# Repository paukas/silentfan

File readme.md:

This is a relay based fan controller.

Arduino switches a relay via pin `PIN_CTL`. Relay inputs are connected to 5V (relay on) and 12V (relay off). Switching is based on temperature received from PC over Serail PORT. PC writes GPU temperature as string to serial port on regular intervals. If arduino fails to receive or parse temperature reading it goes to an error state and switches relay back to 12V.

Possible error state scenarios:
* Arduino failed to receive temperature readings `MAX_NOSIGNALCNT=5` or more times
* Arduino failed to parse temperature reading
* Temperature reading was out of range [`TEMP_MINPOSSIBLE=25`, `TEMP_MAXPOSSIBLE=80`]

Arduino switches relay on only when temperature is below `TEMP_LOW=50`. It switches relay off if temperature reches `TEMP_HIGH=55`.

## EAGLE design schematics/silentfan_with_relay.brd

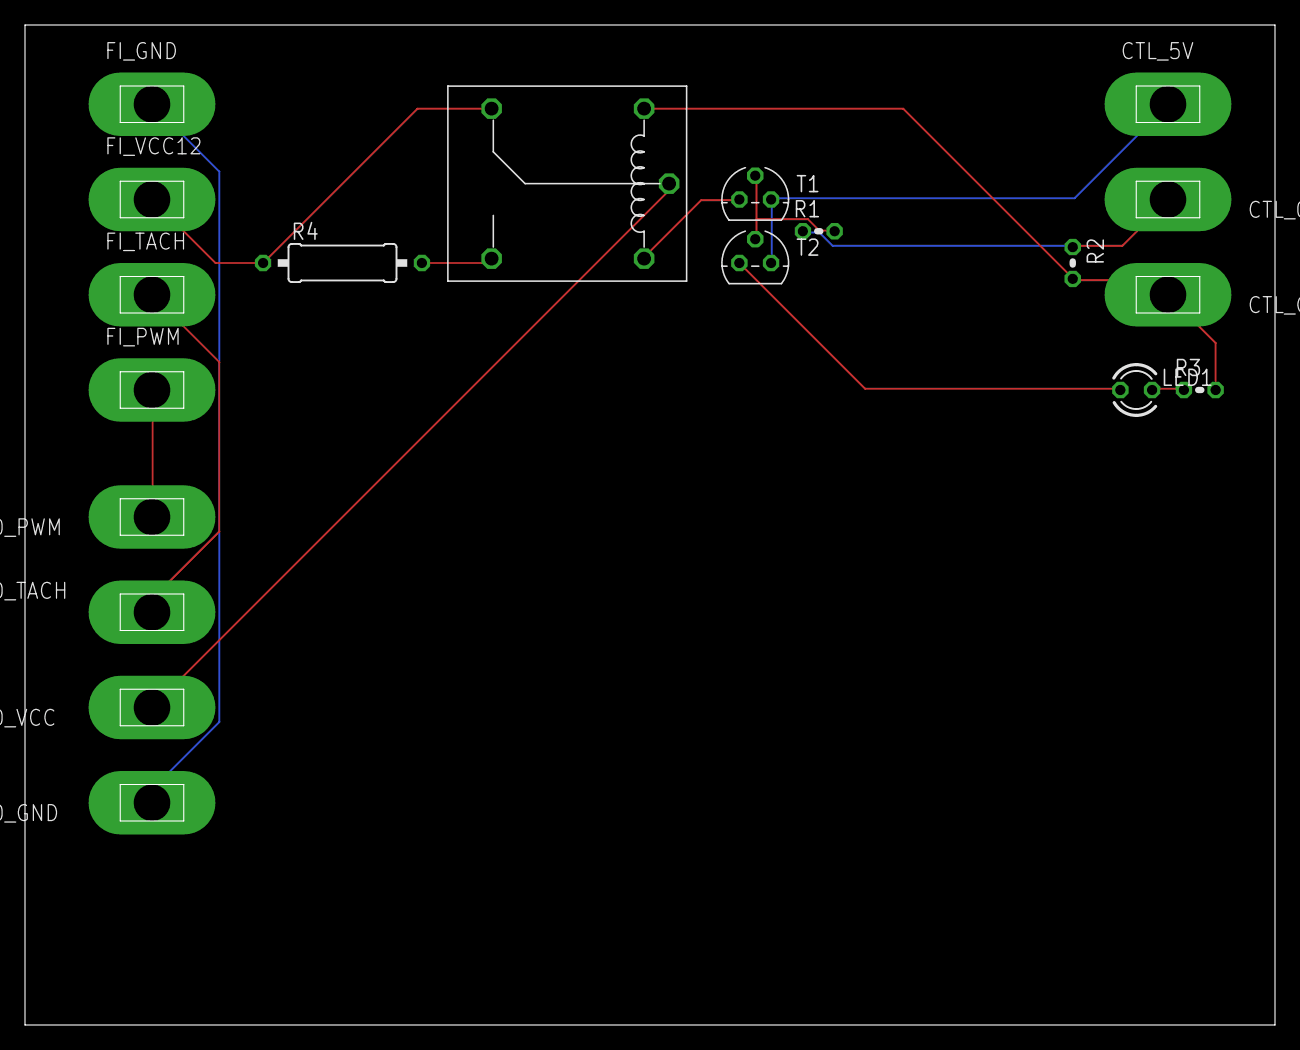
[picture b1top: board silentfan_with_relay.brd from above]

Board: 2 copper layers, 100.0 x 80.0 mm, 19 parts (0 on the bottom side), 13 nets.

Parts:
CTL_5V: PIN1-2; 62221
CTL_GND: PIN1-2; 62221
CTL_ON_OFF_5V: PIN1-2; 62221
FI_GND: PIN1-2; 62221
FI_PWM: PIN1-2; 62221
FI_TACH: PIN1-2; 62221
FI_VCC12: PIN1-2; 62221
FO_GND: PIN1-2; 62221
FO_PWM: PIN1-2; 62221
FO_TACH: PIN1-2; 62221
FO_VCC: PIN1-2; 62221
LED1: LED3MM
R1, R3: 1k; 0204V
R2: 10k; 0204V
R4: 100; 0309/12
T1, T2: 2N3904; TO92
U$1: RELAY

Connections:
unnamed: FI_VCC12.1, R4.1, U$1.COM-CLOSE
unnamed: R4.2, U$1.COM_CPEN
unnamed: FI_TACH.1, FO_TACH.1
unnamed: FI_PWM.1, FO_PWM.1
unnamed: FI_GND.1, FO_GND.1
unnamed: R1.2, T1.2, T2.2
unnamed: CTL_ON_OFF_5V.1, R1.1, R2.1
unnamed: FO_VCC.1, U$1.COM
unnamed: CTL_GND.1, R2.2, R3.2, U$1.P$2
unnamed: T1.3, U$1.P$1
unnamed: LED1.A, T2.3
unnamed: LED1.K, R3.1
unnamed: CTL_5V.1, T1.1, T2.1

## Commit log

2019-09-07 Readme
2019-09-14 Update schematics and configs
2019-09-14 Update schematic
2019-09-16 Add some POC schematics
2019-09-16 Better layout schematics
2019-09-21 Add silent mode delay
2019-10-23 Auto detect COM port
2019-10-23 Update some props
2019-10-23 Add todo file
2019-10-25 WIP: build in installer UI
2019-10-27 Move classes to separate files
2019-10-27 Add an MVP version of installer
2019-10-27 Add --run flag to startup
2019-10-27 Wait for process to exit after killing it so that copy of files does not start when process is running
2019-10-27 Gracefully stop process during installation
2020-01-04 Add two ways of calculating rpm
2020-01-04 Print fan RPM to serial
2020-01-04 Read PWM from serial and set fan duty cycle
2020-01-04 Update gputempmon to swith duty cycle based on temperature and display duty cycle and rpm values retrieved from arduino
2020-01-08 Add support for multiple fans
2020-01-09 Add a hacky setup for FAN2_RPM_PIN on PB4
2020-01-10 Fixes RPM interrupts and pwm fan2 pwm
2020-01-10 Clean up a little but
2020-01-10 Remove unused classes
2020-01-10 Add noctua pwm spec
2020-01-10 Add multiple fan support to PC software
2020-01-11 Add smooth fan curve
2020-01-11 Fix a bug where windows console displayed an empty line between each text line
2020-03-27 Add multi-fan support
